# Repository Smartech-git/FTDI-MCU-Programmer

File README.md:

# FTDI-MCU-Programmer
Designed with KiCad V6.0.6

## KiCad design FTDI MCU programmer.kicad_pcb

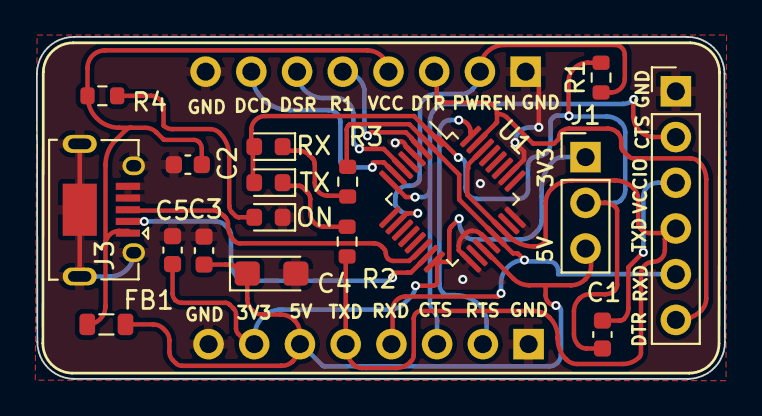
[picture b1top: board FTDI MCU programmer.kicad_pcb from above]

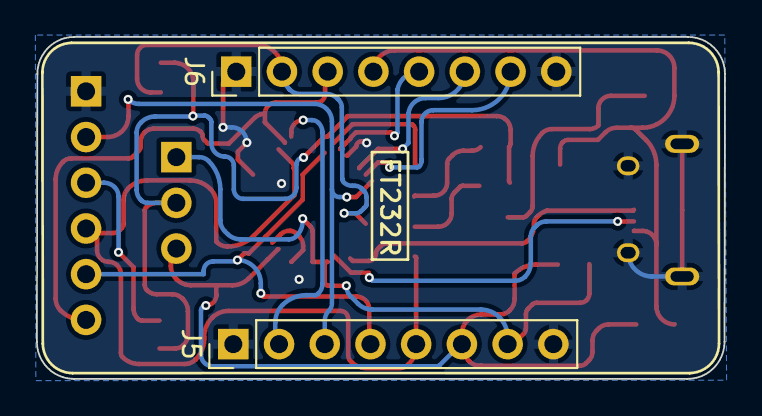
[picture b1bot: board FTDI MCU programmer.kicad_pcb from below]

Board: 2 copper layers, 38.2 x 19.0 mm, 19 parts (2 on the bottom side), 20 nets.

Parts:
C1, C3, C5: 100nF; C_0603_1608Metric
C2: 10nF; C_0603_1608Metric
C4: 4.7uF; CP_EIA-3216-10_Kemet-I
FB1: FerriteBead_Small; L_0805_2012Metric
J1: VCC MCU Select; PinHeader_1x03_P2.54mm_Vertical
J2: MCU IO; PinHeader_1x06_P2.54mm_Vertical
J3: USB_B_Micro; USB_Micro-AB_Molex_47590-0001
J5, J6: BreadBoard IO; PinHeader_1x08_P2.54mm_Vertical
ON: LED(BLUE); LED_0603_1608Metric
R1: 10K; R_0603_1608Metric
R2, R3, R4: 270R; R_0603_1608Metric
RX: LED(YELLOW); LED_0603_1608Metric
TX: LED(RED); LED_0603_1608Metric
U1: FT232RQ; LQFP-32_5x5mm_P0.5mm

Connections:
/3V3: C5.1, J1.1, J5.7, U1.16 (3V3OUT)
/5V: C3.2, C4.1, FB1.2, J1.3, J5.6, U1.19 (VCC)
/CTS: J2.2, J5.3, U1.8 (CTS#)
/DCD: J6.7, U1.7 (DCD#)
/DSR: J6.6, U1.6 (DSR#)
/DTR: J2.6, J6.3, U1.31 (DTR#)
/PWREN: J6.2, R1.1, U1.10 (CBUS2)
/R1: J6.5, U1.3 (R1#)
/RTS: J5.2, U1.32 (RTS#)
/RXD: J2.5, J5.4, R3.2, U1.2 (RXD), U1.21 (CBUS1)
/TXD: J2.4, J5.5, R2.2, U1.22 (CBUS0), U1.30 (TXD)
/VCCIO: C1.2, J1.2, R1.2, RX.2 (A), TX.2 (A), U1.1 (VCCIO)
GND: C2.1, C3.1, C4.2, C5.2, J2.1, J3.4 (ID), J3.5 (GND), J3.6 (Shield), J5.1, J5.8, J6.1, J6.8, ON.1 (K), U1.4 (GND), U1.17 (GND), U1.20 (GND), U1.24 (AGND), U1.26 (TEST)
unnamed: C1.1, J2.3
unnamed: R2.1, TX.1 (K)
unnamed: R3.1, RX.1 (K)
unnamed: ON.2 (A), R4.1
USBDM: J3.2 (D-), U1.15 (USBDM)
USBDP: J3.3 (D+), U1.14 (USBDP)
VBUS: C2.2, FB1.1, J3.1 (VBUS), J6.4, R4.2

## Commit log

2022-08-14 fixed a trace error
2022-08-14 updated image
